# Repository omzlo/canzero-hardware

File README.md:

# Canzero Hardware

This repository contains the design files and schematics of the Omzlo CANZERO, an Arduino-compatible CAN-bus node.

See: http://omzlo.com/canzero

This work is licensed under the [Creative Commons Attribution-ShareAlike 4.0 International Public License][1].

[1]: https://creativecommons.org/licenses/by-sa/4.0/

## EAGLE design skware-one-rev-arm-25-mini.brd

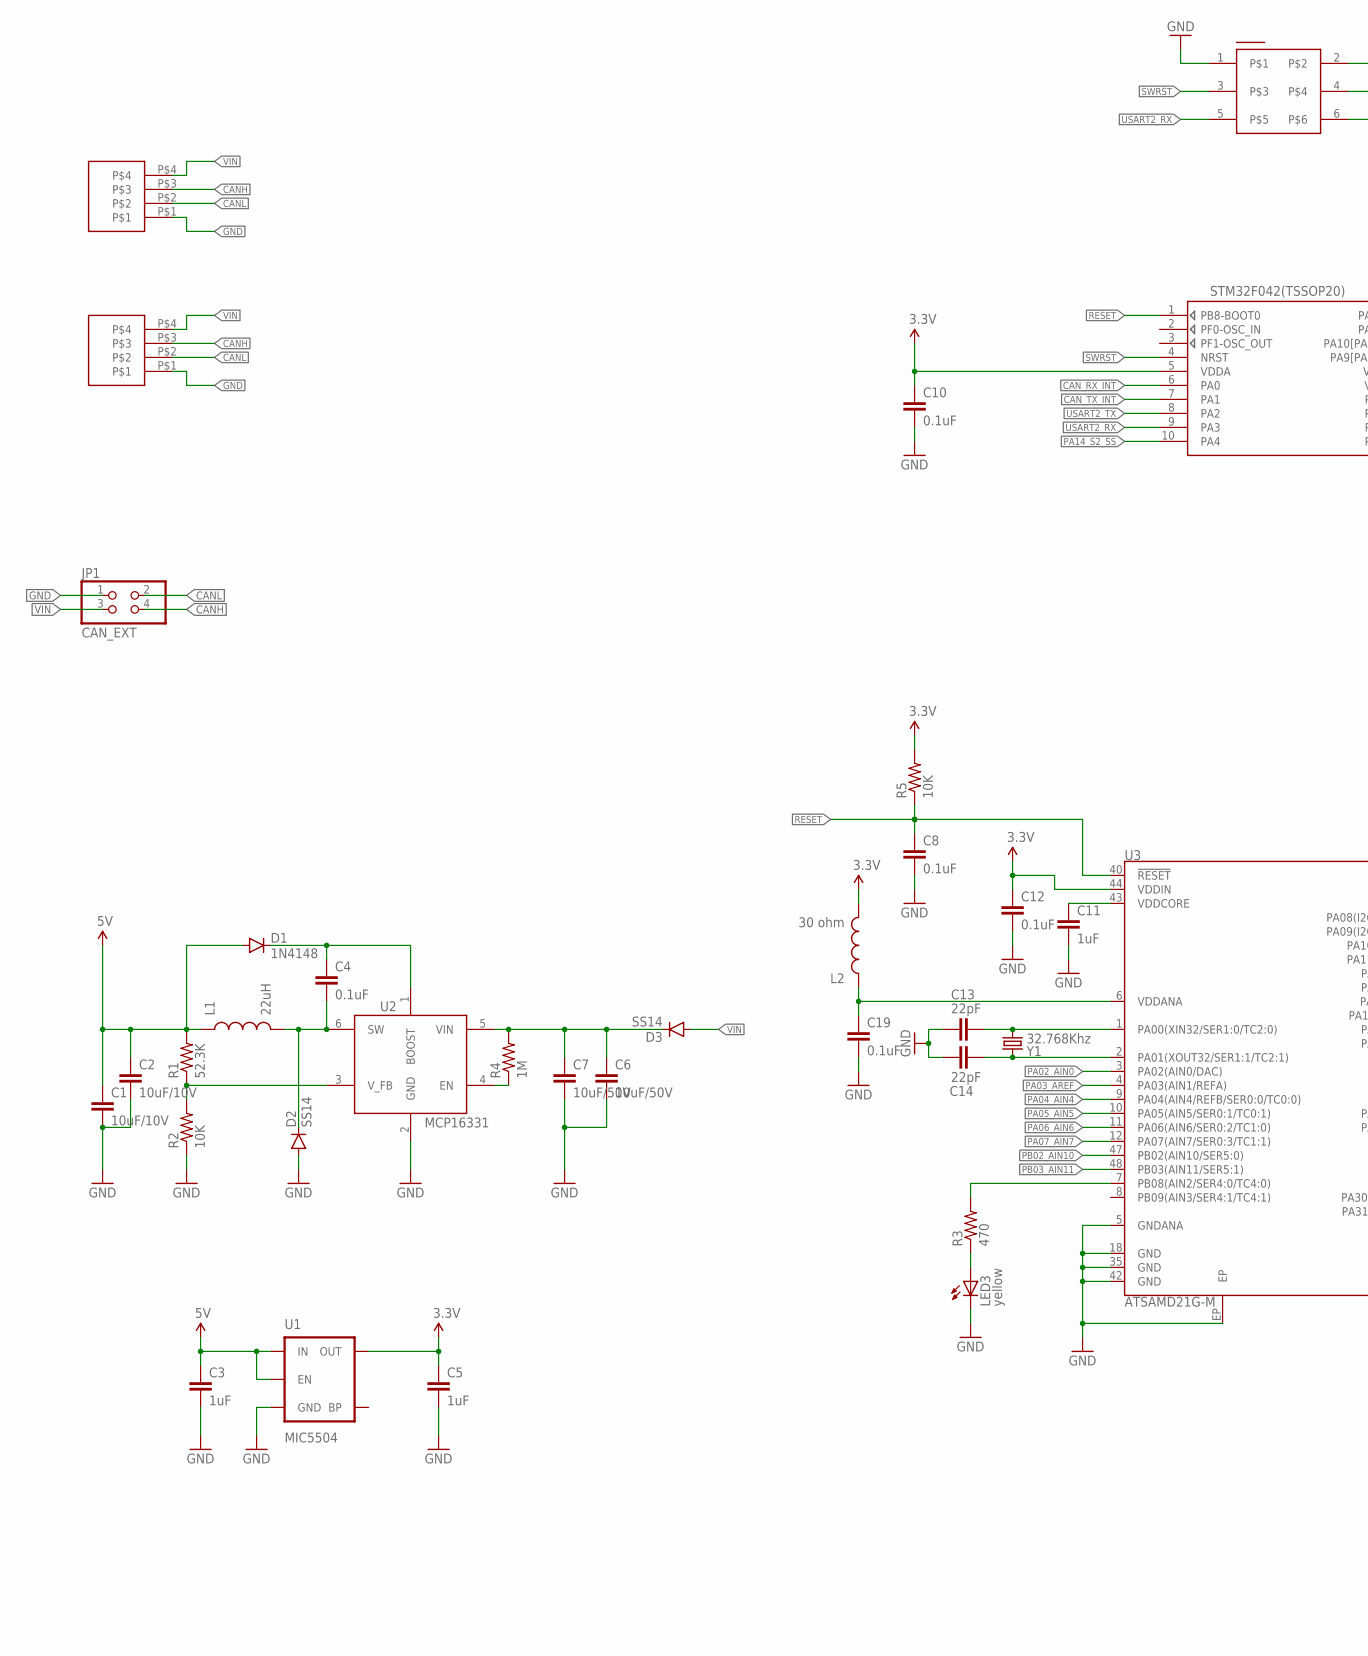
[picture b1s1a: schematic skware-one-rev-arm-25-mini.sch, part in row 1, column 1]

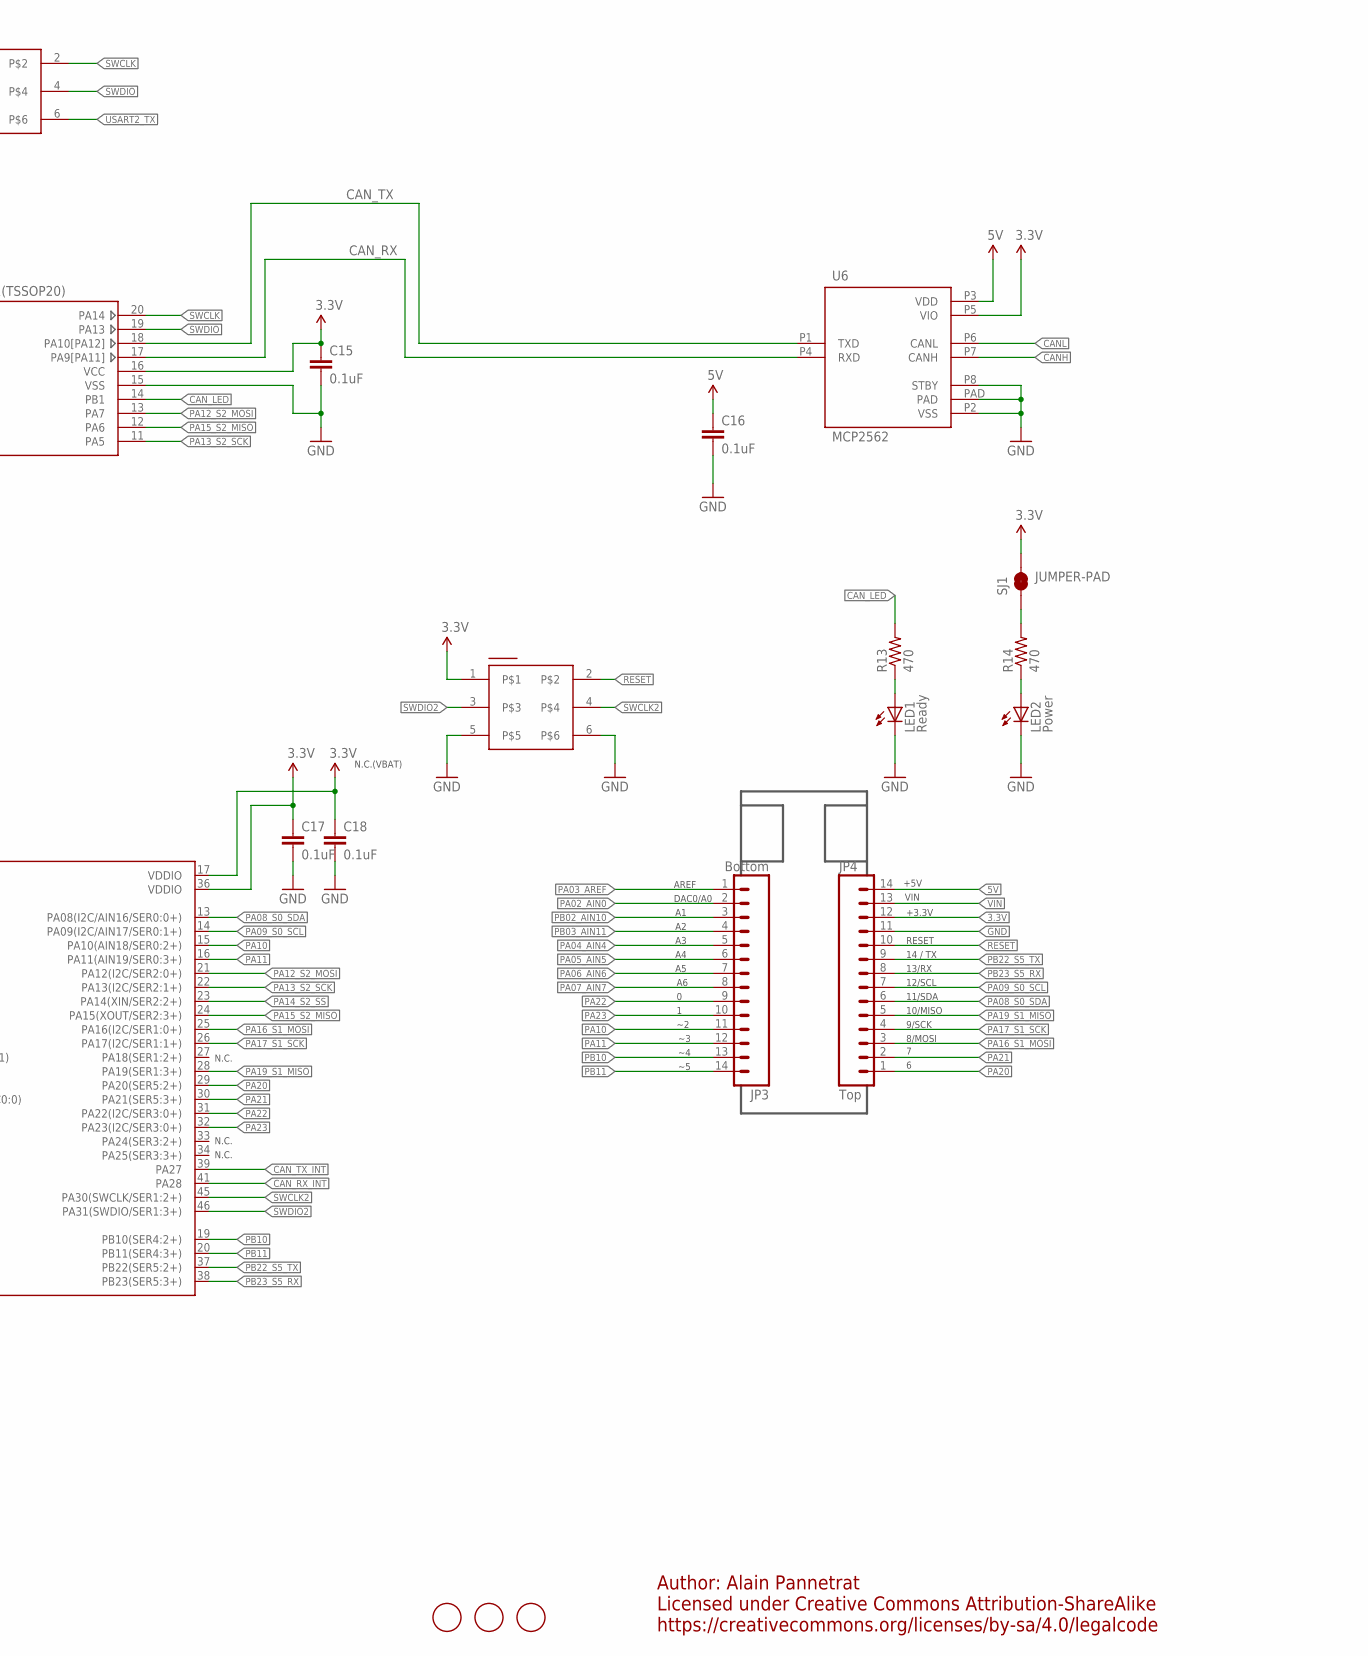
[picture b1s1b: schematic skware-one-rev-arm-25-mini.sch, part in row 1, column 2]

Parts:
C1, C2: 10uF/10V; 0805
C3, C5, C11: 1uF; 0805
C4, C8, C10, C12, C15, C16, C17, C18, C19: 0.1uF; 0603-CAP
C6, C7: 10uF/50V; 1206
C13, C14: 22pF; 0805
D1: 1N4148; SOD-323
D2, D3: SS14; SMA-DIODE_ALT
JP1: CAN_EXT; 2X02
JP3: Bottom; 1X14
JP4: Top; 1X14
L1: 22uH; SRN6045
L2: 30 ohm; 0603
LED1: Ready; SML0805
LED2: Power; SML0805
LED3: yellow; SML0805
R1: 52.3K; 0805
R2, R5: 10K; 0805
R3, R13, R14: 470; 0603-RES
R4: 1M; 0805
SJ1: JUMPER-PAD; PAD-JUMPER-2-NC_BY_TRACE_YES_SILK
U1: MIC5504; SOT23-5
U2: MCP16331; SOT23-6
U3: ATSAMD21G-M; QFN-48
U4: STM32F042(TSSOP20); TSSOP20
U6: MCP2562; DFN3X3
U$1, U$3: M04-PLUG-3.5
U$4, U$5: 3X2-SMT-PROG; 2X3-SMT-HEAD
U$6, U$7, U$8: FIDUCIAL; FIDUCIAL_1MM
Y1: 32.768Khz; CRYSTAL-SMD-3.2X1.5MM

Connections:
3.3V: C5.1, C10.1, C12.1, C15.1, C17.1, C18.1, JP4.12, L2.2, R5.2, SJ1.2, U1.5 (OUT), U3.17 (VDDIO), U3.36 (VDDIO), U3.44 (VDDIN), U4.5 (VDDA), U4.16 (VCC), U6.P5 (VIO), U$4.1
5V: C1.1, C2.1, C3.1, C16.1, D1.A, JP4.14, L1.1, R1.2, U1.1 (IN), U1.3 (EN), U6.P3 (VDD)
A1: R3.2, U3.7 (PB08(AIN2/SER4:0/TC4:0))
CANH: JP1.4, U6.P7 (CANH), U$1.P$3, U$3.P$3
CANL: JP1.2, U6.P6 (CANL), U$1.P$2, U$3.P$2
CAN_LED: R13.2, U4.14 (PB1)
CAN_RX: U4.17 (PA9[PA11]), U6.P4 (RXD)
CAN_RX_INT: U3.41 (PA28), U4.6 (PA0)
CAN_TX: U4.18 (PA10[PA12]), U6.P1 (TXD)
CAN_TX_INT: U3.39 (PA27), U4.7 (PA1)
GND: C1.2, C2.2, C3.2, C5.2, C6.2, C7.2, C8.2, C10.2, C11.2, C12.2, C13.1, C14.1, C15.2, C16.2, C17.2, C18.2, C19.2, D2.A, JP1.1, JP4.11, LED1.C, LED2.C, LED3.C, R2.1, U1.2 (GND), U2.2 (GND), U3.5 (GNDANA), U3.18 (GND), U3.35 (GND), U3.42 (GND), U3.EP, U4.15 (VSS), U6.P2 (VSS), U6.P8 (STBY), U6.PAD, U$1.P$1, U$3.P$1, U$4.5, U$4.6, U$5.1
unnamed: R4.1, U2.4 (EN)
unnamed: C11.1, U3.43 (VDDCORE)
unnamed: C13.2, U3.1 (PA00(XIN32/SER1:0/TC2:0)), Y1.P$2 (2)
unnamed: C14.2, U3.2 (PA01(XOUT32/SER1:1/TC2:1)), Y1.P$1 (1)
unnamed: C19.1, L2.1, U3.6 (VDDANA)
unnamed: R14.2, SJ1.1
unnamed: LED2.A, R14.1
unnamed: C6.1, C7.1, D3.C, R4.2, U2.5 (VIN)
unnamed: LED3.A, R3.1
unnamed: LED1.A, R13.1
unnamed: R1.1, R2.2, U2.3 (V_FB)
unnamed: C4.2, D2.C, L1.2, U2.6 (SW)
unnamed: C4.1, D1.C, U2.1 (BOOST)
PA02_AIN0: JP3.2, U3.3 (PA02(AIN0/DAC))
PA03_AREF: JP3.1, U3.4 (PA03(AIN1/REFA))
PA04_AIN4: JP3.5, U3.9 (PA04(AIN4/REFB/SER0:0/TC0:0))
PA05_AIN5: JP3.6, U3.10 (PA05(AIN5/SER0:1/TC0:1))
PA06_AIN6: JP3.7, U3.11 (PA06(AIN6/SER0:2/TC1:0))
PA07_AIN7: JP3.8, U3.12 (PA07(AIN7/SER0:3/TC1:1))
PA08_S0_SDA: JP4.6, U3.13 (PA08(I2C/AIN16/SER0:0+))
PA09_S0_SCL: JP4.7, U3.14 (PA09(I2C/AIN17/SER0:1+))
PA10: JP3.11, U3.15 (PA10(AIN18/SER0:2+))
PA11: JP3.12, U3.16 (PA11(AIN19/SER0:3+))
PA12_S2_MOSI: U3.21 (PA12(I2C/SER2:0+)), U4.13 (PA7)
PA13_S2_SCK: U3.22 (PA13(I2C/SER2:1+)), U4.11 (PA5)
PA14_S2_SS: U3.23 (PA14(XIN/SER2:2+)), U4.10 (PA4)
PA15_S2_MISO: U3.24 (PA15(XOUT/SER2:3+)), U4.12 (PA6)
PA16_S1_MOSI: JP4.3, U3.25 (PA16(I2C/SER1:0+))
PA17_S1_SCK: JP4.4, U3.26 (PA17(I2C/SER1:1+))
PA19_S1_MISO: JP4.5, U3.28 (PA19(SER1:3+))
PA20: JP4.1, U3.29 (PA20(SER5:2+))
PA21: JP4.2, U3.30 (PA21(SER5:3+))
PA22: JP3.9, U3.31 (PA22(I2C/SER3:0+))
PA23: JP3.10, U3.32 (PA23(I2C/SER3:0+))
PB02_AIN10: JP3.3, U3.47 (PB02(AIN10/SER5:0))
PB03_AIN11: JP3.4, U3.48 (PB03(AIN11/SER5:1))
PB10: JP3.13, U3.19 (PB10(SER4:2+))
PB11: JP3.14, U3.20 (PB11(SER4:3+))
PB22_S5_TX: JP4.9, U3.37 (PB22(SER5:2+))
PB23_S5_RX: JP4.8, U3.38 (PB23(SER5:3+))
RESET: C8.1, JP4.10, R5.1, U3.40 (!RESET!), U4.1 (PB8-BOOT0), U$4.2
SWCLK: U4.20 (PA14), U$5.2
SWCLK2: U3.45 (PA30(SWCLK/SER1:2+)), U$4.4
SWDIO: U4.19 (PA13), U$5.4
SWDIO2: U3.46 (PA31(SWDIO/SER1:3+)), U$4.3
SWRST: U4.4 (NRST), U$5.3
USART2_RX: U4.9 (PA3), U$5.5
USART2_TX: U4.8 (PA2), U$5.6
VIN: D3.A, JP1.3, JP4.13, U$1.P$4, U$3.P$4

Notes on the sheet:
N.C.(VBAT)
AREF
DAC0/A0
+5V
VIN
+3.3V
RESET
14 / TX
13/RX
12/SCL
11/SDA
10/MISO
9/SCK
8/MOSI
N.C.
Author: Alain Pannetrat Licensed under Creative Commons Attribution-ShareAlike https://creativecommons.org/licenses/by-sa/4.0/legalcode

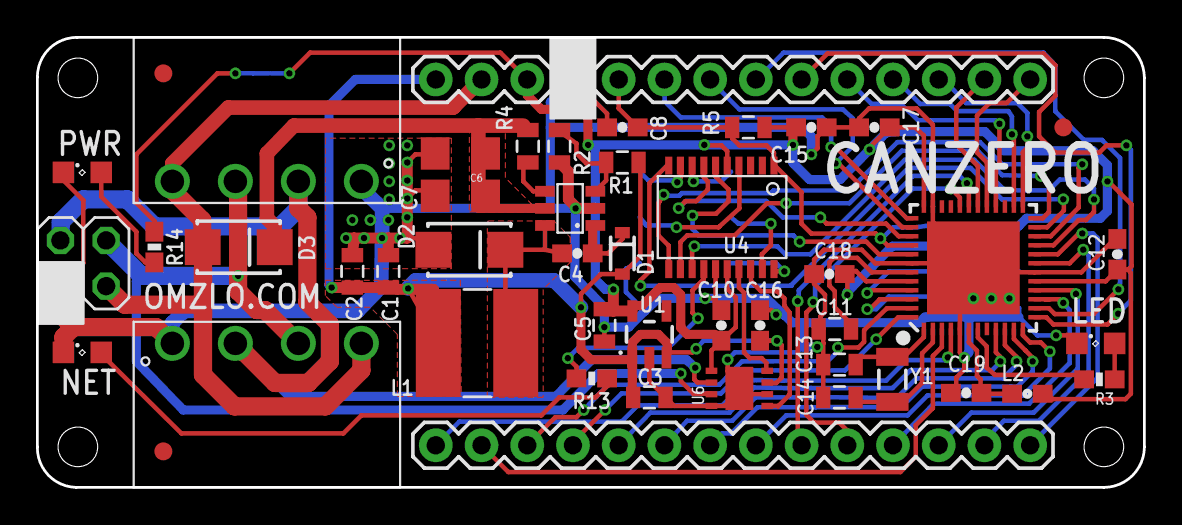
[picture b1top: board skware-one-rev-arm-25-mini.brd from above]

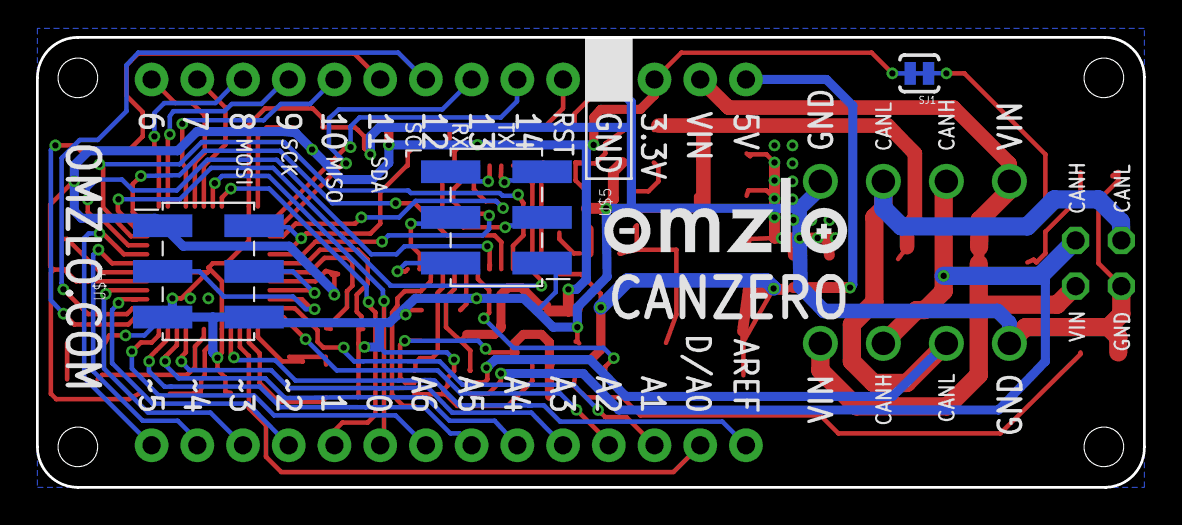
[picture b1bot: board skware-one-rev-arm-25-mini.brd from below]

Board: 2 copper layers, 61.5 x 25.0 mm, 51 parts (4 on the bottom side), 60 nets.

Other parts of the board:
U$2: OMZLO-0.5

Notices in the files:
parts and their libraries:
SparkFun-Capacitors: Licensing: Creative Commons ShareAlike 4.0 International - https://creativecommons.org/licenses/by-sa/4.0
